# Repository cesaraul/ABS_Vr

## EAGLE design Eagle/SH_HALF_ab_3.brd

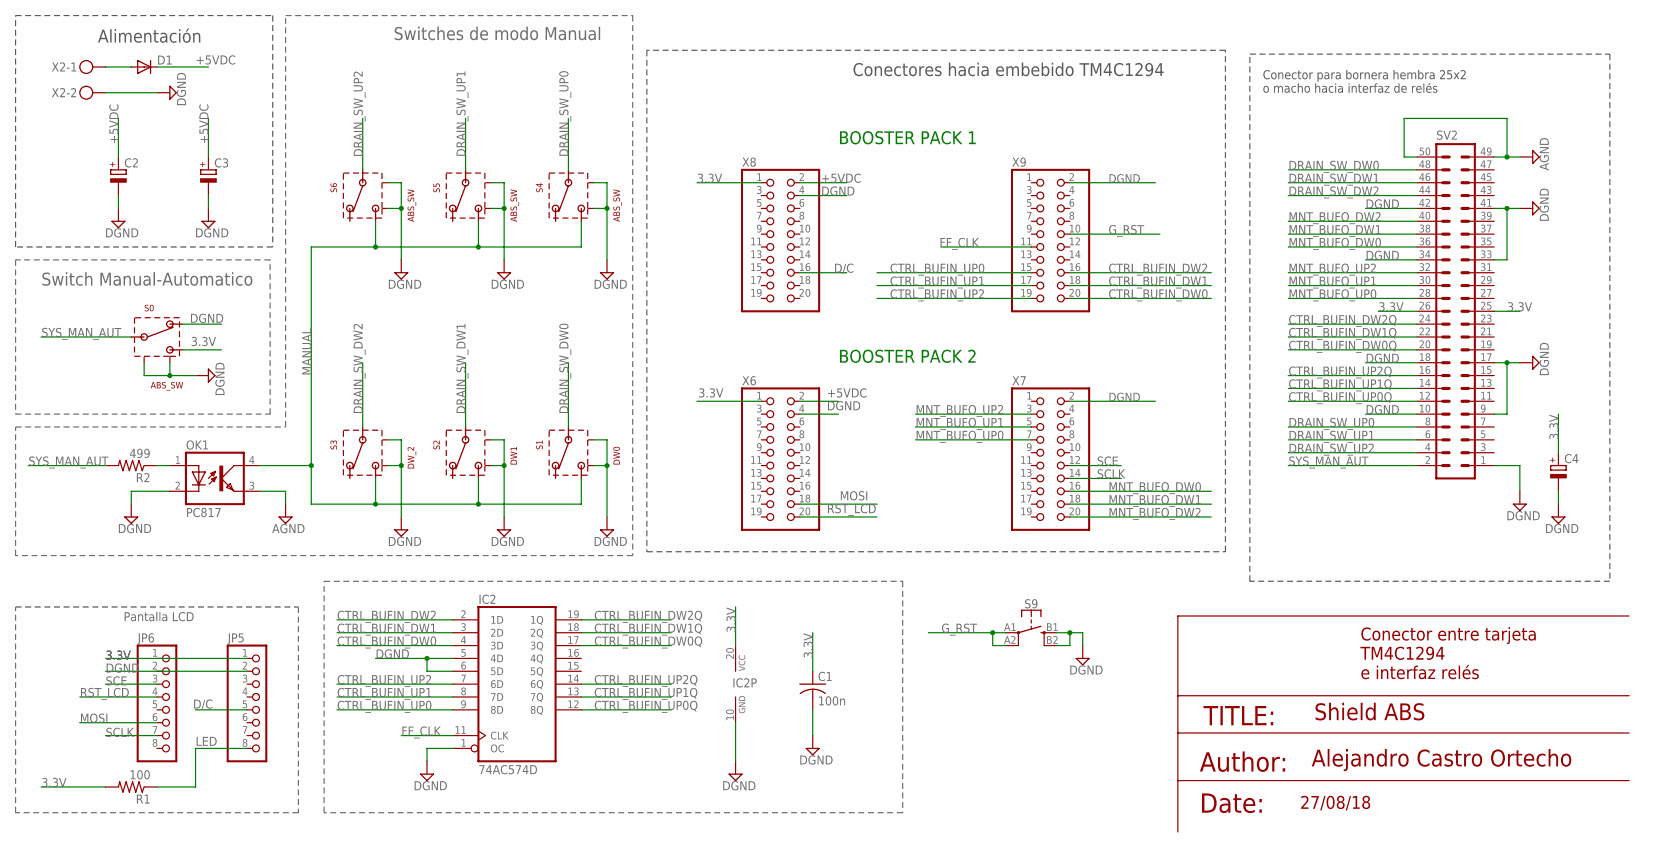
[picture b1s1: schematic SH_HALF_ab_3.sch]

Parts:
C1: 100n; C0805K
C2, C3, C4: CPOL-EUB/3528-21R; B/3528-21R
D1: DIODE-SMBSMB; SMB
IC2: 74AC574D; SO20W
JP5, JP6: PINHD-1X8; 1X08
OK1: PC817; DIL04
R1: 100; R1206
R2: 499; R1206
S0, S4, S5, S6: ABS_SW
S1: DW0; ABS_SW
S2: DW1; ABS_SW
S3: DW_2; ABS_SW
S9: MOMENTARY-SWITCH-SPST-2; TACTILE_SWITCH_SMD_6.2MM_TALL
SV2: ML50F; ML50_F
X2: MKDSN1,5/2-5,08
X6, X7, X8, X9: PINHD-2X10; 2X10

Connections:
3.3V: C1.1, C4.+, IC2.20 (VCC), JP5.1, JP6.1, R1.2, S0.3, SV2.25, SV2.26, X6.1, X8.1
+5VDC: C2.+, C3.+, D1.C, X6.2, X8.2
AGND: OK1.3 (EMIT), SV2.49, SV2.50
CTRL_BUFIN_DW0: IC2.4 (3D), X9.20
CTRL_BUFIN_DW0Q: IC2.17 (3Q), SV2.20
CTRL_BUFIN_DW1: IC2.3 (2D), X9.18
CTRL_BUFIN_DW1Q: IC2.18 (2Q), SV2.22
CTRL_BUFIN_DW2: IC2.2 (1D), X9.16
CTRL_BUFIN_DW2Q: IC2.19 (1Q), SV2.24
CTRL_BUFIN_UP0: IC2.9 (8D), X9.15
CTRL_BUFIN_UP0Q: IC2.12 (8Q), SV2.12
CTRL_BUFIN_UP1: IC2.8 (7D), X9.17
CTRL_BUFIN_UP1Q: IC2.13 (7Q), SV2.14
CTRL_BUFIN_UP2: IC2.7 (6D), X9.19
CTRL_BUFIN_UP2Q: IC2.14 (6Q), SV2.16
D/C: JP5.5, X8.16
DGND: C1.2, C2.-, C3.-, C4.-, IC2.1 (OC), IC2.5 (4D), IC2.6 (5D), IC2.10 (GND), JP5.2, JP6.2, OK1.2 (C), S0.1, S0.M1 (GND), S0.M2 (GND1), S1.M1 (GND), S1.M2 (GND1), S2.M1 (GND), S2.M2 (GND1), S3.M1 (GND), S3.M2 (GND1), S4.M1 (GND), S4.M2 (GND1), S5.M1 (GND), S5.M2 (GND1), S6.M1 (GND), S6.M2 (GND1), S9.B1 (3), S9.B2 (4), SV2.1, SV2.9, SV2.10, SV2.17, SV2.18, SV2.33, SV2.34, SV2.41, SV2.42, X2.2, X6.4, X7.2, X8.4, X9.2
DRAIN_SW_DW0: S1.2, SV2.48
DRAIN_SW_DW1: S2.2, SV2.46
DRAIN_SW_DW2: S3.2, SV2.44
DRAIN_SW_UP0: S4.2, SV2.8
DRAIN_SW_UP1: S5.2, SV2.6
DRAIN_SW_UP2: S6.2, SV2.4
FF_CLK: IC2.11 (CLK), X9.11
G_RST: S9.A1 (1), S9.A2 (2), X9.10
LED: JP5.8, R1.1
MANUAL: OK1.4 (COL), S1.3, S2.3, S3.3, S4.3, S5.3, S6.3
MNT_BUFO_DW0: SV2.36, X7.16
MNT_BUFO_DW1: SV2.38, X7.18
MNT_BUFO_DW2: SV2.40, X7.20
MNT_BUFO_UP0: SV2.28, X7.7
MNT_BUFO_UP1: SV2.30, X7.5
MNT_BUFO_UP2: SV2.32, X7.3
MOSI: JP6.6, X6.18
unnamed: D1.A, X2.1
unnamed: OK1.1 (A), R2.1
RST_LCD: JP6.4, X6.20
SCE: JP6.3, X7.12
SCLK: JP6.7, X7.14
SYS_MAN_AUT: R2.2, S0.2, SV2.2

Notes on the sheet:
Conector para bornera hembra 25x2 o macho hacia interfaz de relés
Conectores hacia embebido TM4C1294
Alimentación
Conector entre tarjeta TM4C1294 e interfaz relés
Pantalla LCD
Shield ABS
TITLE:
Alejandro Castro Ortecho
Author:
Date:
27/08/18
Switch Manual-Automatico
Switches de modo Manual
BOOSTER PACK 1
BOOSTER PACK 2

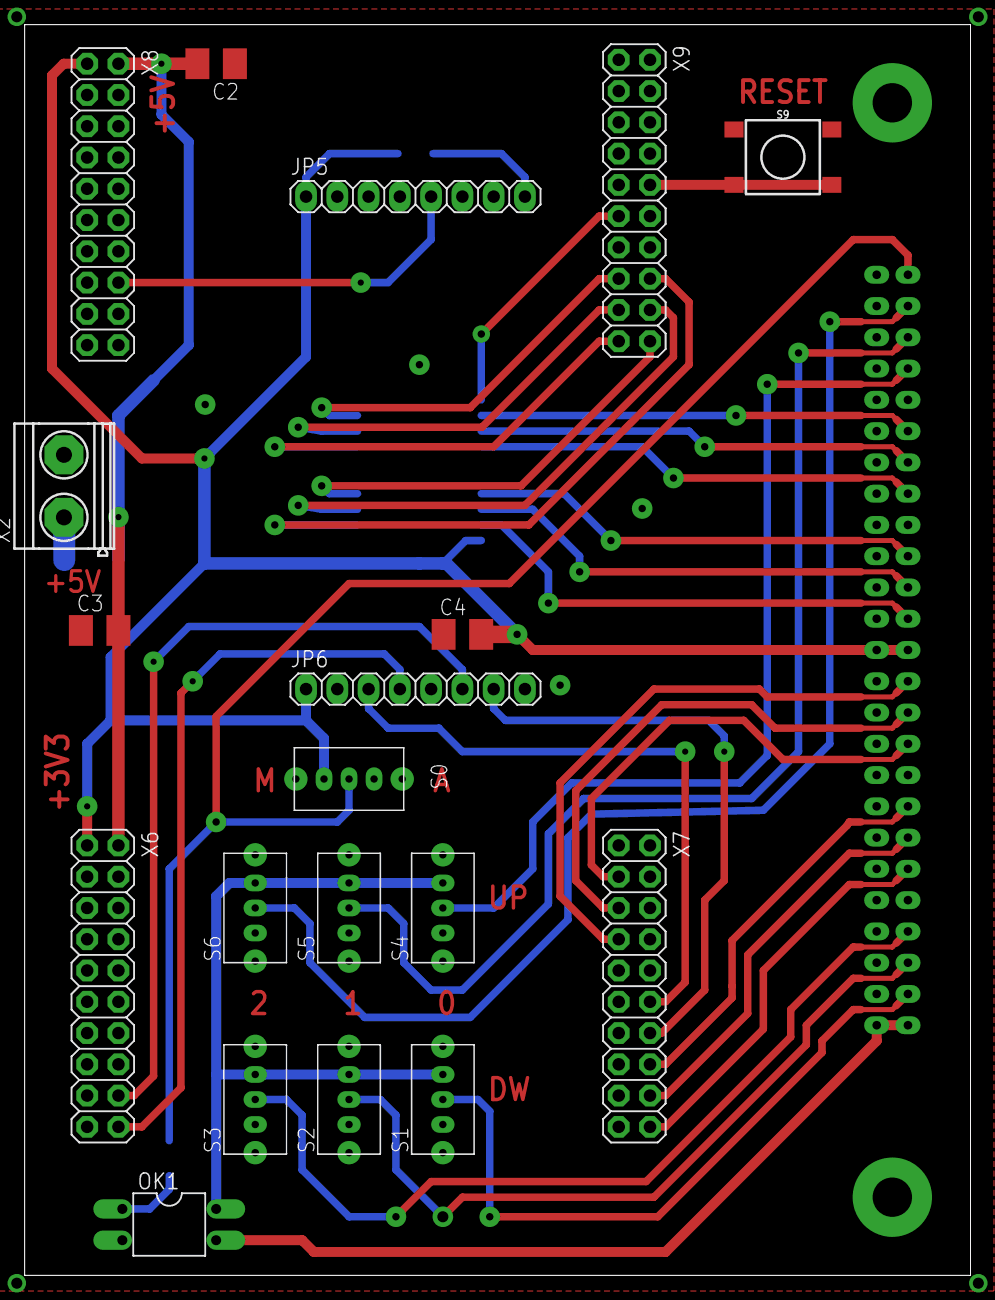
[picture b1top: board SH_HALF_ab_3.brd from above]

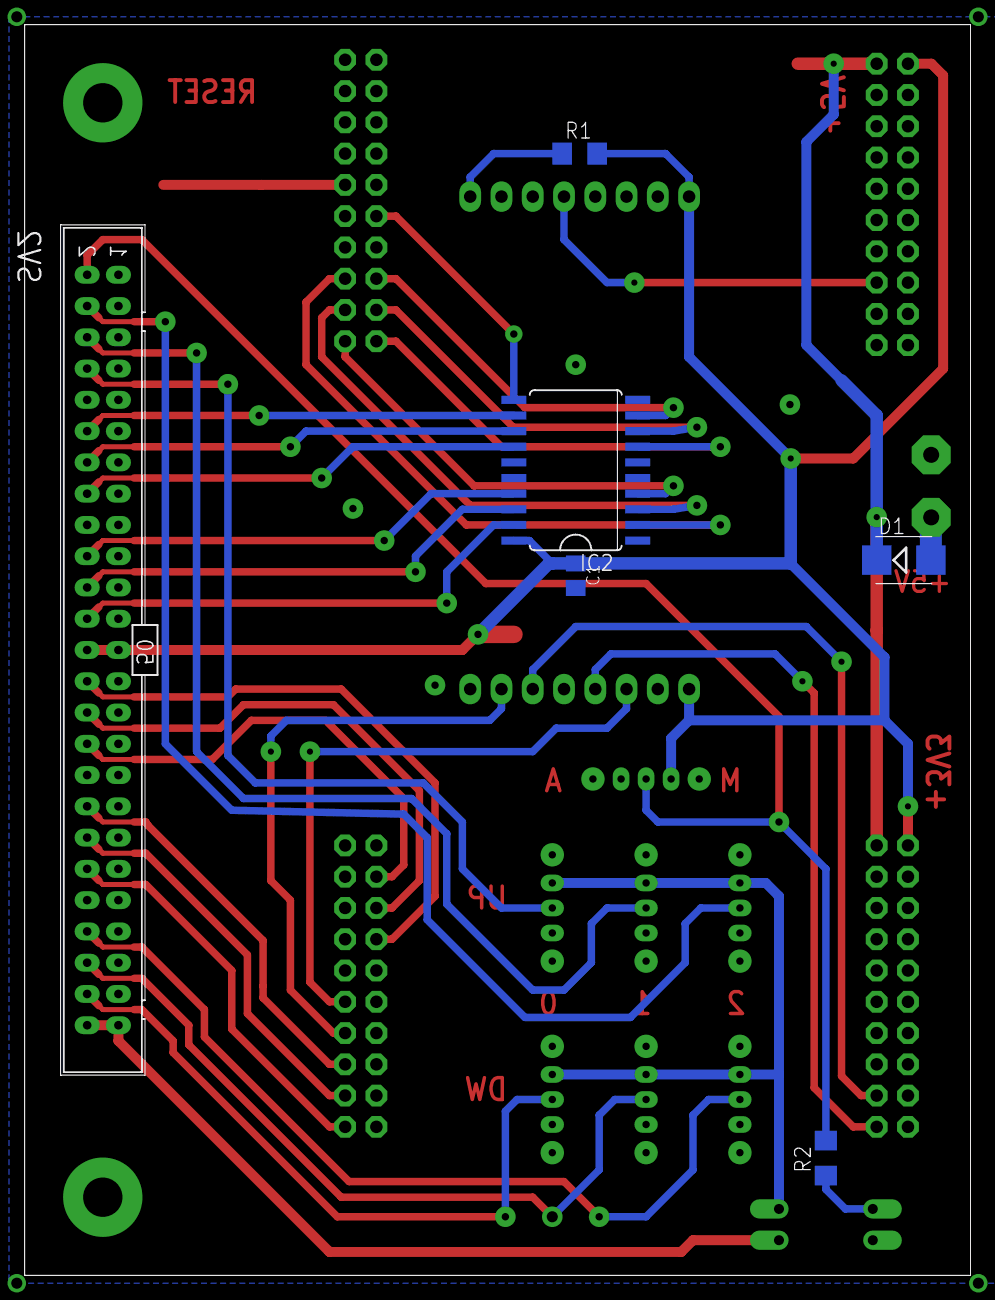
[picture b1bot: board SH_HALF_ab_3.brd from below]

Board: 2 copper layers, 76.8 x 101.6 mm, 25 parts (5 on the bottom side), 40 nets.

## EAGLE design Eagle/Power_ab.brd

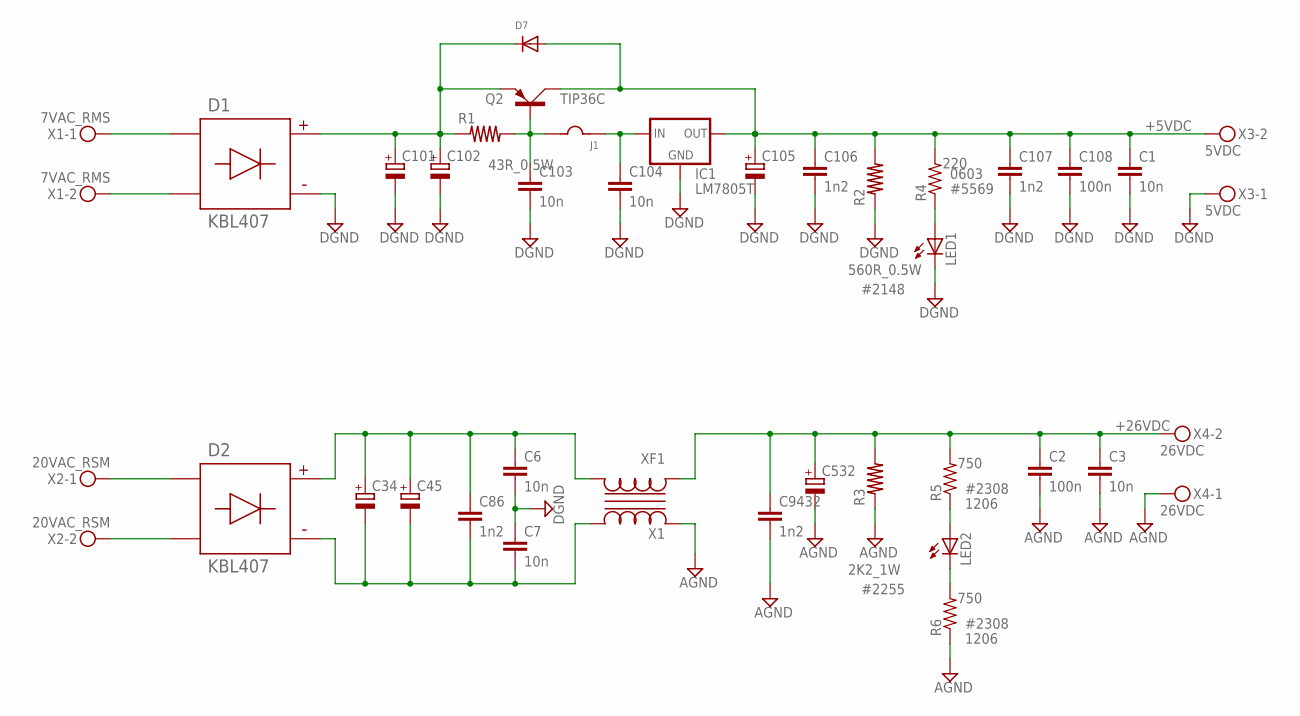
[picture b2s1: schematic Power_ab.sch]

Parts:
C1, C3, C6, C7, C103, C104: 10n; C1206
C2, C108: 100n; C1206
C34, C45, C532: CPOL-EUEB20C; EB20C
C86, C106, C107, C9432: 1n2; C075-032X103
C101, C102, C105: CPOL-EUE7.5-18; E7,5-18
D1, D2: KBL407; KBL
D7: 1N4007; DO-41
IC1: LM7805T; 78XXS
J1: JUMP350MILS; JUMP350
LED1, LED2: LED5MM
Q2: TIP36C; TOP3AV
R1: 43R_0.5W; 50R500
R2: 560R_0.5W; 50R500
R3: 2K2_1W; 50R500
R4: 220; R0603
R5, R6: 750; R1206
X1: 7VAC_RMS; MKDSN1,5/2-5,08
X2: 20VAC_RSM; MKDSN1,5/2-5,08
X3: 5VDC; MKDSN1,5/2-5,08
X4: 26VDC; MKDSN1,5/2-5,08
XF1: X1; TORO1

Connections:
+5VDC: C1.1, C105.+, C106.1, C107.1, C108.1, D7.A (ANODE), IC1.OUT, Q2.C, R2.P$2, R4.2, X3.2
+26VDC: C2.1, C3.1, C532.+, C9432.1, R3.P$2, R5.2, X4.2, XF1.L1A
AGND: C2.2, C3.2, C532.-, C9432.2, R3.P$1, R6.1, X4.1, XF1.L2A
DGND: C1.2, C6.2, C7.1, C101.-, C102.-, C103.2, C104.2, C105.-, C106.2, C107.2, C108.2, D1.-, IC1.GND, LED1.K (C), R2.P$1, X3.1
unnamed: C101.+, C102.+, D1.+, D7.K (KATODE), Q2.E, R1.P$1
unnamed: D1.AC1, X1.1
unnamed: D1.AC2, X1.2
unnamed: D2.AC1, X2.1
unnamed: D2.AC2, X2.2
unnamed: C104.1, IC1.IN, J1.P$2
unnamed: C6.1, C34.+, C45.+, C86.1, D2.+, XF1.L1B
unnamed: C103.1, J1.P$1, Q2.B, R1.P$2
unnamed: C7.2, C34.-, C45.-, C86.2, D2.-, XF1.L2B
unnamed: LED1.A, R4.1
unnamed: LED2.A, R5.1
unnamed: LED2.K (C), R6.2

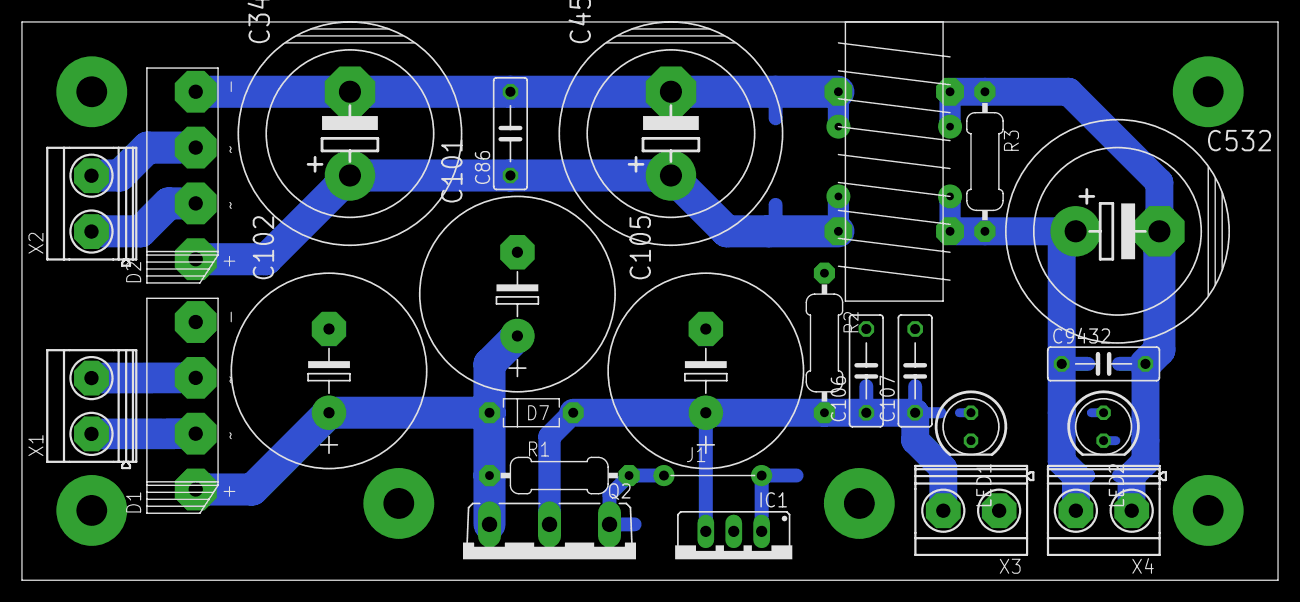
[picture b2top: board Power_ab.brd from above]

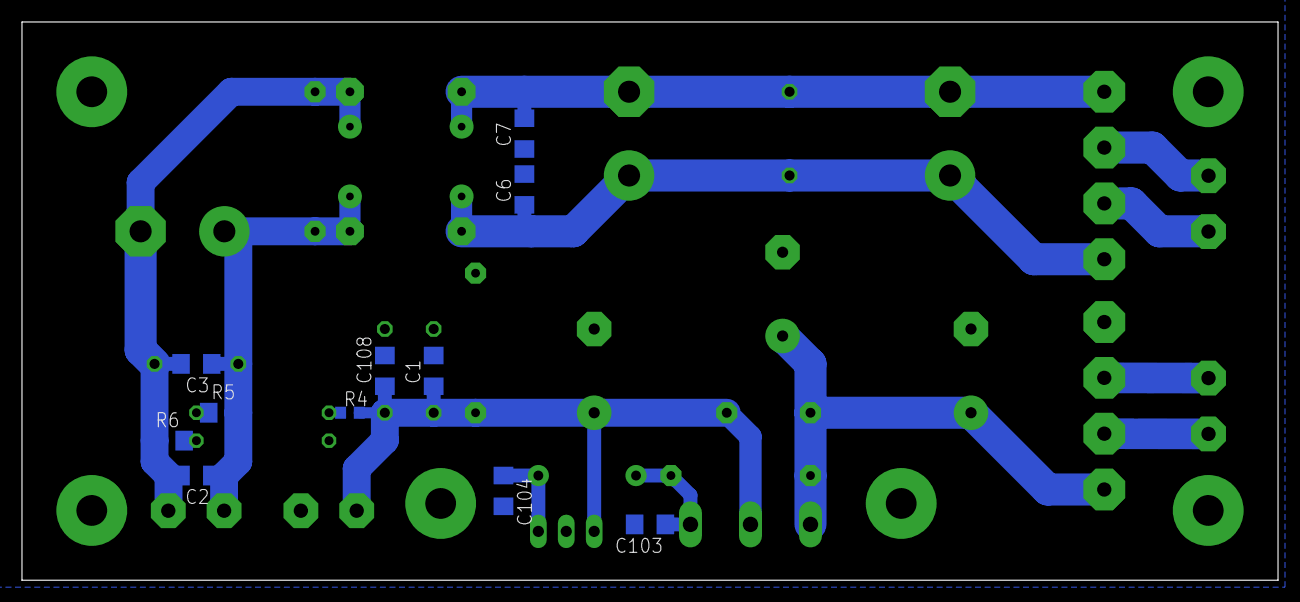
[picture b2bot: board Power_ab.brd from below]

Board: 2 copper layers, 114.3 x 50.8 mm, 37 parts (11 on the bottom side), 16 nets.

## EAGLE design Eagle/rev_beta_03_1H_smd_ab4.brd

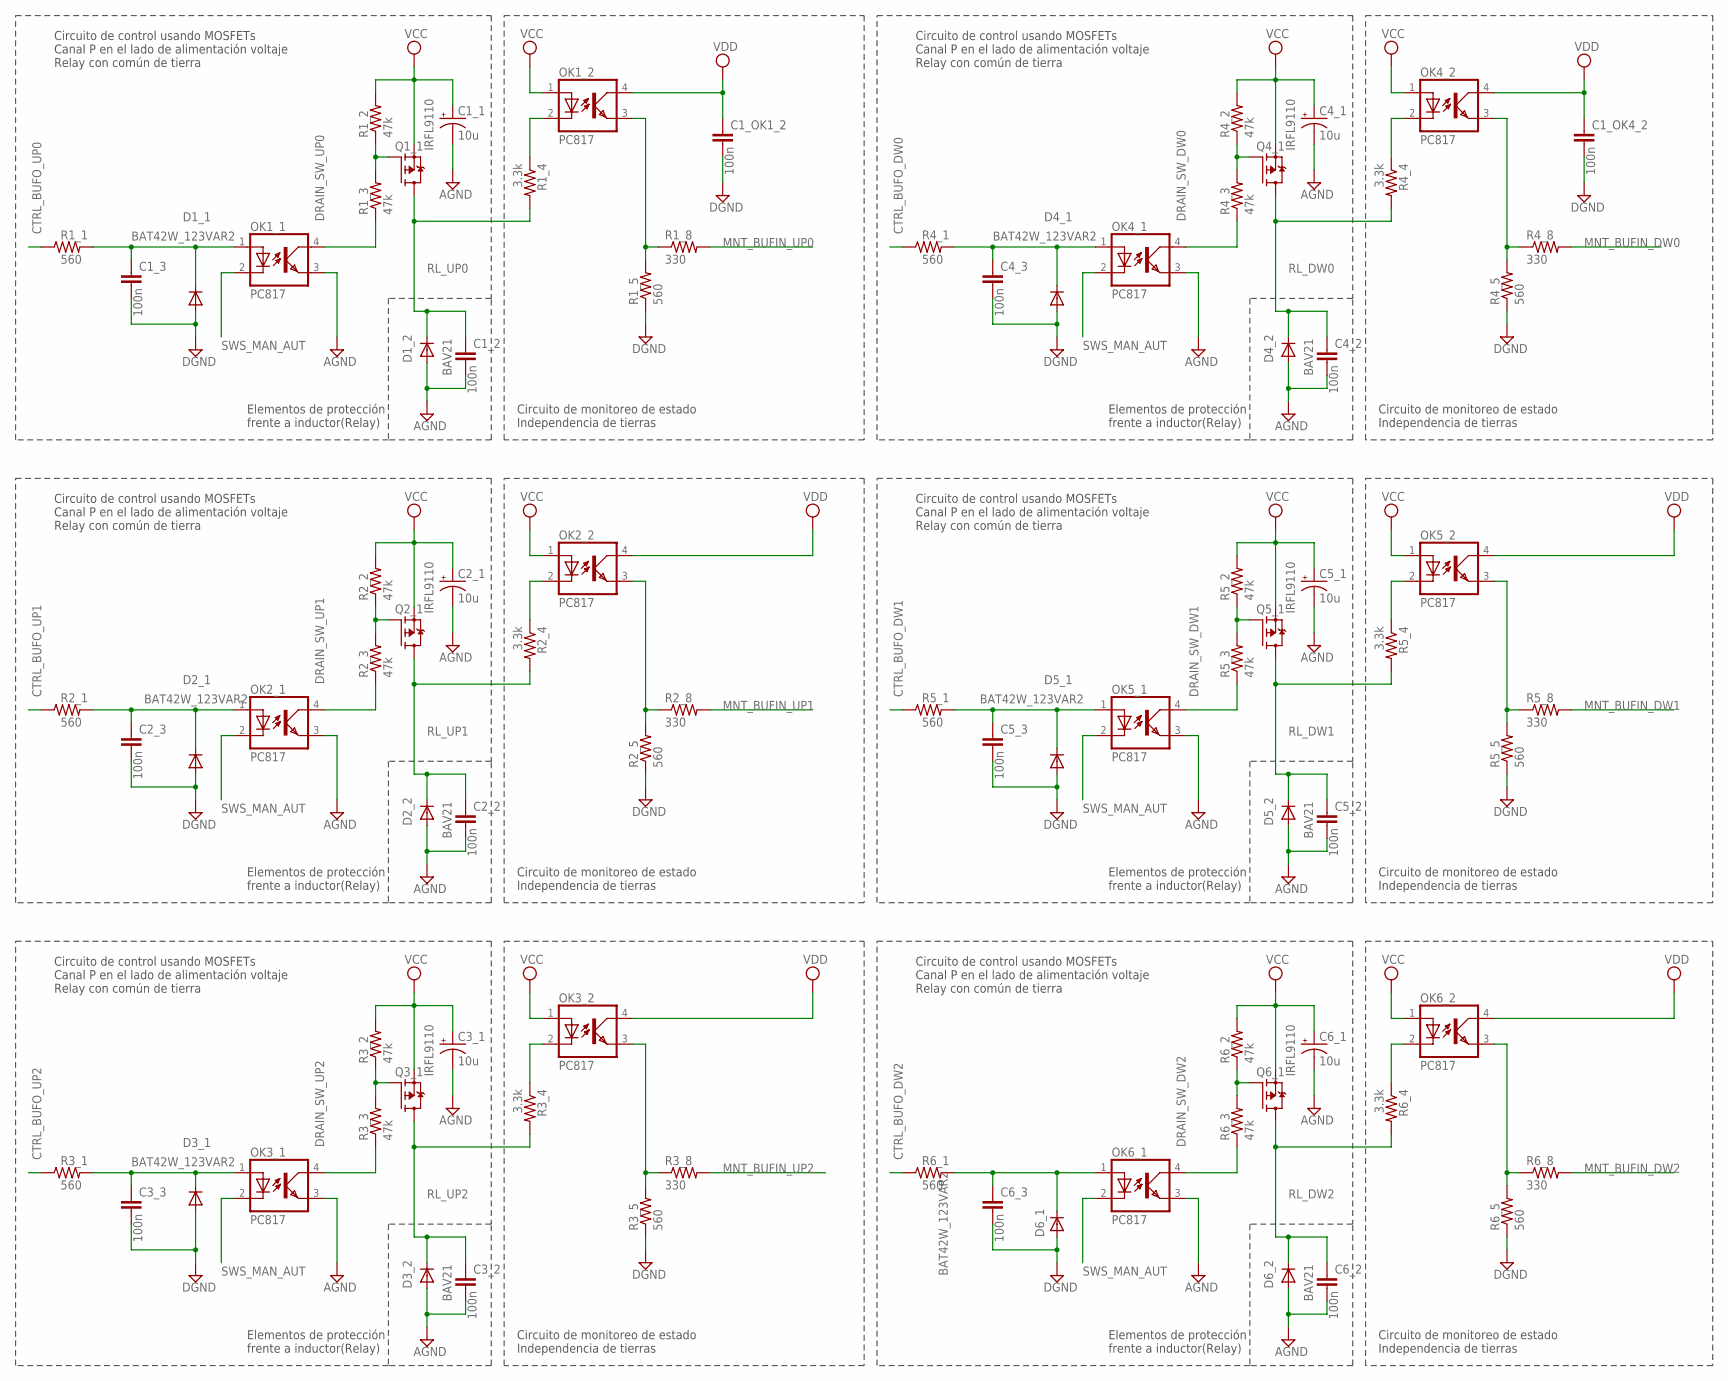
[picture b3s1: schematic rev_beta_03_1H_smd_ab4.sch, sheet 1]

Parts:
C1_1, C2_1, C3_1, C4_1, C5_1, C6_1: 10u; 153CLV-0605
C1_2, C1_3, C1_OK1_2, C1_OK4_2, C2_2, C2_3, C3_2, C3_3, C4_2, C4_3, C5_2, C5_3, C6_2, C6_3: 100n; C1206
D1_1, D2_1, D3_1, D4_1, D5_1, D6_1: BAT42W_123VAR2; SOD-523F
D1_2, D2_2, D3_2, D4_2, D5_2, D6_2: BAV21; DO-35
OK1_1, OK1_2, OK2_1, OK2_2, OK3_1, OK3_2, OK4_1, OK4_2, OK5_1, OK5_2, OK6_1, OK6_2: PC817; DIL04
Q1_1, Q2_1, Q3_1, Q4_1, Q5_1, Q6_1: IRFL9110; SOT-223
R1_1, R1_5, R2_1, R2_5, R3_1, R3_5, R4_1, R4_5, R5_1, R5_5, R6_1, R6_5: 560; R1206
R1_2, R2_2, R3_2, R4_2, R5_2, R6_2: 47k; 0207/10
R1_3, R2_3, R3_3, R4_3, R5_3, R6_3: 47k; R1206
R1_4, R2_4, R3_4, R4_4, R5_4, R6_4: 3.3k; R1206
R1_8, R2_8, R3_8, R4_8, R5_8, R6_8: 330; R1206

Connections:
AGND: C1_1.-, C1_2.2, C2_1.-, C2_2.2, C3_1.-, C3_2.2, C4_1.-, C4_2.2, C5_1.-, C5_2.2, C6_1.-, C6_2.2, D1_2.A, D2_2.A, D3_2.A, D4_2.A, D5_2.A, D6_2.A, OK1_1.3 (EMIT), OK2_1.3 (EMIT), OK3_1.3 (EMIT), OK4_1.3 (EMIT), OK5_1.3 (EMIT), OK6_1.3 (EMIT); also elsewhere on the board
CTRL_BUFO_DW0: R4_1.1; also elsewhere on the board
CTRL_BUFO_DW1: R5_1.1; also elsewhere on the board
CTRL_BUFO_DW2: R6_1.1; also elsewhere on the board
CTRL_BUFO_UP0: R1_1.1; also elsewhere on the board
CTRL_BUFO_UP1: R2_1.1; also elsewhere on the board
CTRL_BUFO_UP2: R3_1.1; also elsewhere on the board
DGND: C1_3.2, C1_OK1_2.2, C1_OK4_2.2, C2_3.2, C3_3.2, C4_3.2, C5_3.2, C6_3.2, D1_1.A (1), D2_1.A (1), D3_1.A (1), D4_1.A (1), D5_1.A (1), D6_1.A (1), R1_5.1, R2_5.1, R3_5.1, R4_5.1, R5_5.1, R6_5.1; also elsewhere on the board
DRAIN_SW_DW0: OK4_1.4 (COL), R4_3.1; also elsewhere on the board
DRAIN_SW_DW1: OK5_1.4 (COL), R5_3.1; also elsewhere on the board
DRAIN_SW_DW2: OK6_1.4 (COL), R6_3.1; also elsewhere on the board
DRAIN_SW_UP0: OK1_1.4 (COL), R1_3.1; also elsewhere on the board
DRAIN_SW_UP1: OK2_1.4 (COL), R2_3.1; also elsewhere on the board
DRAIN_SW_UP2: OK3_1.4 (COL), R3_3.1; also elsewhere on the board
GATE-M/A-UP0: C1_3.1, D1_1.C (2), OK1_1.1 (A), R1_1.2
GATE-M/A-UP1: C2_3.1, D2_1.C (2), OK2_1.1 (A), R2_1.2
GATE-M/A-UP2: C3_3.1, D3_1.C (2), OK3_1.1 (A), R3_1.2
GATE-M/A-UP3: C4_3.1, D4_1.C (2), OK4_1.1 (A), R4_1.2
GATE-M/A-UP4: C5_3.1, D5_1.C (2), OK5_1.1 (A), R5_1.2
GATE-M/A-UP5: C6_3.1, D6_1.C (2), OK6_1.1 (A), R6_1.2
MNT_BUFIN_DW0: R4_8.2; also elsewhere on the board
MNT_BUFIN_DW1: R5_8.2; also elsewhere on the board
MNT_BUFIN_DW2: R6_8.2; also elsewhere on the board
MNT_BUFIN_UP0: R1_8.2; also elsewhere on the board
MNT_BUFIN_UP1: R2_8.2; also elsewhere on the board
MNT_BUFIN_UP2: R3_8.2; also elsewhere on the board
unnamed: Q2_1.1 (G), R2_2.1, R2_3.2
unnamed: OK2_2.3 (EMIT), R2_5.2, R2_8.1
unnamed: OK1_2.2 (C), R1_4.1
unnamed: Q1_1.1 (G), R1_2.1, R1_3.2
unnamed: OK2_2.2 (C), R2_4.1
unnamed: OK1_2.3 (EMIT), R1_5.2, R1_8.1
unnamed: Q3_1.1 (G), R3_2.1, R3_3.2
unnamed: OK3_2.3 (EMIT), R3_5.2, R3_8.1
unnamed: OK3_2.2 (C), R3_4.1
unnamed: Q4_1.1 (G), R4_2.1, R4_3.2
unnamed: OK4_2.3 (EMIT), R4_5.2, R4_8.1
unnamed: OK4_2.2 (C), R4_4.1
unnamed: Q5_1.1 (G), R5_2.1, R5_3.2
unnamed: OK5_2.3 (EMIT), R5_5.2, R5_8.1
unnamed: OK5_2.2 (C), R5_4.1
unnamed: Q6_1.1 (G), R6_2.1, R6_3.2
unnamed: OK6_2.3 (EMIT), R6_5.2, R6_8.1
unnamed: OK6_2.2 (C), R6_4.1
RL_DW0: C4_2.1, D4_2.C, Q4_1.2 (D), Q4_1.4 (D), R4_4.2; also elsewhere on the board
RL_DW1: C5_2.1, D5_2.C, Q5_1.2 (D), Q5_1.4 (D), R5_4.2; also elsewhere on the board
RL_DW2: C6_2.1, D6_2.C, Q6_1.2 (D), Q6_1.4 (D), R6_4.2; also elsewhere on the board
RL_UP0: C1_2.1, D1_2.C, Q1_1.2 (D), Q1_1.4 (D), R1_4.2; also elsewhere on the board
RL_UP1: C2_2.1, D2_2.C, Q2_1.2 (D), Q2_1.4 (D), R2_4.2; also elsewhere on the board
RL_UP2: C3_2.1, D3_2.C, Q3_1.2 (D), Q3_1.4 (D), R3_4.2; also elsewhere on the board
SWS_MAN_AUT: OK1_1.2 (C), OK2_1.2 (C), OK3_1.2 (C), OK4_1.2 (C), OK5_1.2 (C), OK6_1.2 (C); also elsewhere on the board
VCC: C1_1.+, C2_1.+, C3_1.+, C4_1.+, C5_1.+, C6_1.+, OK1_2.1 (A), OK2_2.1 (A), OK3_2.1 (A), OK4_2.1 (A), OK5_2.1 (A), OK6_2.1 (A), Q1_1.3 (S), Q2_1.3 (S), Q3_1.3 (S), Q4_1.3 (S), Q5_1.3 (S), Q6_1.3 (S), R1_2.2, R2_2.2, R3_2.2, R4_2.2, R5_2.2, R6_2.2; also elsewhere on the board
VDD: C1_OK1_2.1, C1_OK4_2.1, OK1_2.4 (COL), OK2_2.4 (COL), OK3_2.4 (COL), OK4_2.4 (COL), OK5_2.4 (COL), OK6_2.4 (COL); also elsewhere on the board

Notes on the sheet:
Circuito de control usando MOSFETs Canal P en el lado de alimentación voltaje Relay con común de tierra
Elementos de protección frente a inductor(Relay)
Circuito de monitoreo de estado Independencia de tierras

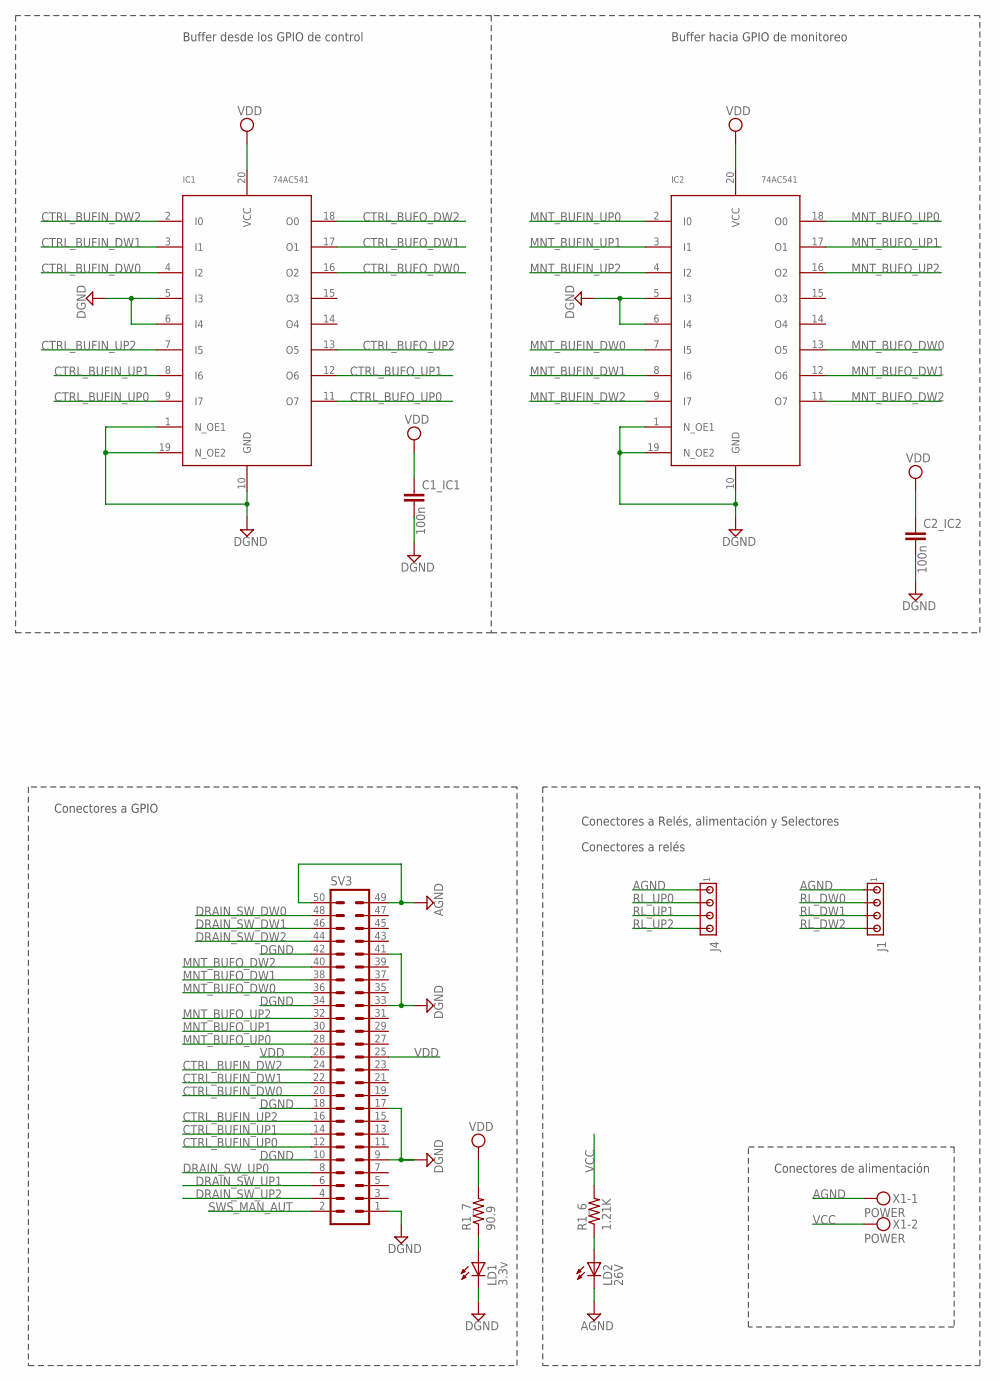
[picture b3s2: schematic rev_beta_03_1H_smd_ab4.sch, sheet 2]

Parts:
C1_IC1, C2_IC2: 100n; C1206
IC1, IC2: 74AC541; SOIC-20DW
J1, J4: MTA04-156; 1X4MTA
LD1: 3.3v; CHIPLED_0603
LD2: 26V; CHIPLED_0603
R1_6: 1.21K; R1206
R1_7: 90.9; R1206
SV3: ML50"; ML50
X1: POWER; MKDSN1,5/2-5,08

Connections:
AGND: J1.1, J4.1, LD2.C, SV3.49, SV3.50, X1.1; also elsewhere on the board
CTRL_BUFIN_DW0: IC1.4 (I2), SV3.20
CTRL_BUFIN_DW1: IC1.3 (I1), SV3.22
CTRL_BUFIN_DW2: IC1.2 (I0), SV3.24
CTRL_BUFIN_UP0: IC1.9 (I7), SV3.12
CTRL_BUFIN_UP1: IC1.8 (I6), SV3.14
CTRL_BUFIN_UP2: IC1.7 (I5), SV3.16
CTRL_BUFO_DW0: IC1.16 (O2); also elsewhere on the board
CTRL_BUFO_DW1: IC1.17 (O1); also elsewhere on the board
CTRL_BUFO_DW2: IC1.18 (O0); also elsewhere on the board
CTRL_BUFO_UP0: IC1.11 (O7); also elsewhere on the board
CTRL_BUFO_UP1: IC1.12 (O6); also elsewhere on the board
CTRL_BUFO_UP2: IC1.13 (O5); also elsewhere on the board
DGND: C1_IC1.2, C2_IC2.2, IC1.1 (N_OE1), IC1.5 (I3), IC1.6 (I4), IC1.10 (GND), IC1.19 (N_OE2), IC2.1 (N_OE1), IC2.5 (I3), IC2.6 (I4), IC2.10 (GND), IC2.19 (N_OE2), LD1.C, SV3.1, SV3.9, SV3.10, SV3.17, SV3.18, SV3.33, SV3.34, SV3.41, SV3.42; also elsewhere on the board
DRAIN_SW_DW0: SV3.48; also elsewhere on the board
DRAIN_SW_DW1: SV3.46; also elsewhere on the board
DRAIN_SW_DW2: SV3.44; also elsewhere on the board
DRAIN_SW_UP0: SV3.8; also elsewhere on the board
DRAIN_SW_UP1: SV3.6; also elsewhere on the board
DRAIN_SW_UP2: SV3.4; also elsewhere on the board
MNT_BUFIN_DW0: IC2.7 (I5); also elsewhere on the board
MNT_BUFIN_DW1: IC2.8 (I6); also elsewhere on the board
MNT_BUFIN_DW2: IC2.9 (I7); also elsewhere on the board
MNT_BUFIN_UP0: IC2.2 (I0); also elsewhere on the board
MNT_BUFIN_UP1: IC2.3 (I1); also elsewhere on the board
MNT_BUFIN_UP2: IC2.4 (I2); also elsewhere on the board
MNT_BUFO_DW0: IC2.13 (O5), SV3.36
MNT_BUFO_DW1: IC2.12 (O6), SV3.38
MNT_BUFO_DW2: IC2.11 (O7), SV3.40
MNT_BUFO_UP0: IC2.18 (O0), SV3.28
MNT_BUFO_UP1: IC2.17 (O1), SV3.30
MNT_BUFO_UP2: IC2.16 (O2), SV3.32
unnamed: LD2.A, R1_6.1
unnamed: LD1.A, R1_7.1
RL_DW0: J1.2; also elsewhere on the board
RL_DW1: J1.3; also elsewhere on the board
RL_DW2: J1.4; also elsewhere on the board
RL_UP0: J4.2; also elsewhere on the board
RL_UP1: J4.3; also elsewhere on the board
RL_UP2: J4.4; also elsewhere on the board
SWS_MAN_AUT: SV3.2; also elsewhere on the board
VCC: R1_6.2, X1.2; also elsewhere on the board
VDD: C1_IC1.1, C2_IC2.1, IC1.20 (VCC), IC2.20 (VCC), R1_7.2, SV3.25, SV3.26; also elsewhere on the board

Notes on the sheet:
Buffer desde los GPIO de control
Buffer hacia GPIO de monitoreo
Conectores a GPIO
Conectores a Relés, alimentación y Selectores
Conectores a relés
Conectores de alimentación

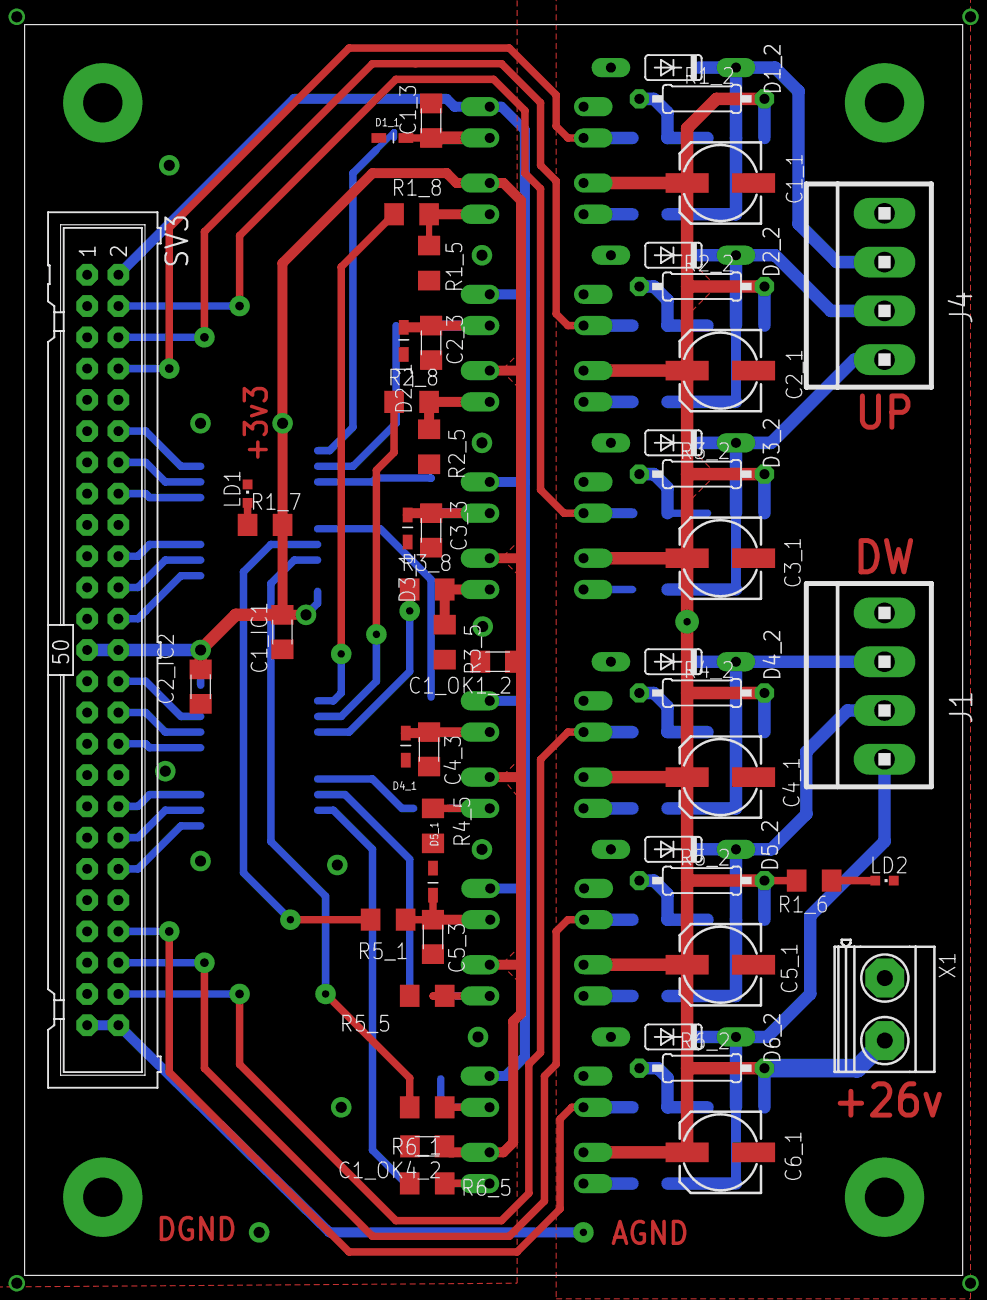
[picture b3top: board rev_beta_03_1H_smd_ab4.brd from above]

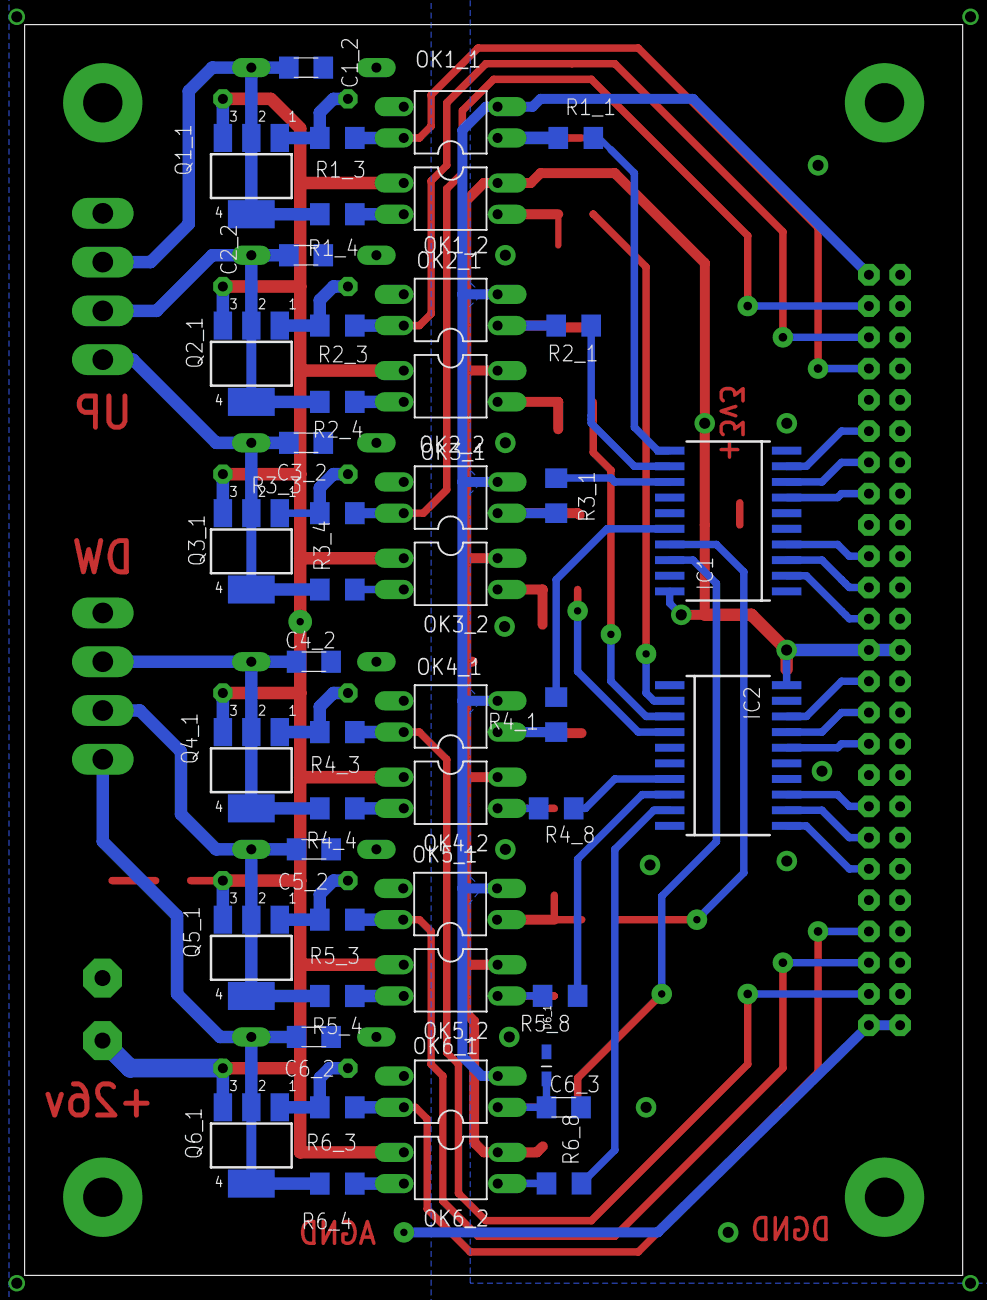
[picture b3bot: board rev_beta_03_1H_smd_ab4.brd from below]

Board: 2 copper layers, 76.2 x 101.6 mm, 98 parts (47 on the bottom side), 67 nets.

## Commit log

2019-03-05 TEST_sonar

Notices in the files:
parts and their libraries:
SparkFun-Switches: Licensing: Creative Commons ShareAlike 4.0 International - https://creativecommons.org/licenses/by-sa/4.0
